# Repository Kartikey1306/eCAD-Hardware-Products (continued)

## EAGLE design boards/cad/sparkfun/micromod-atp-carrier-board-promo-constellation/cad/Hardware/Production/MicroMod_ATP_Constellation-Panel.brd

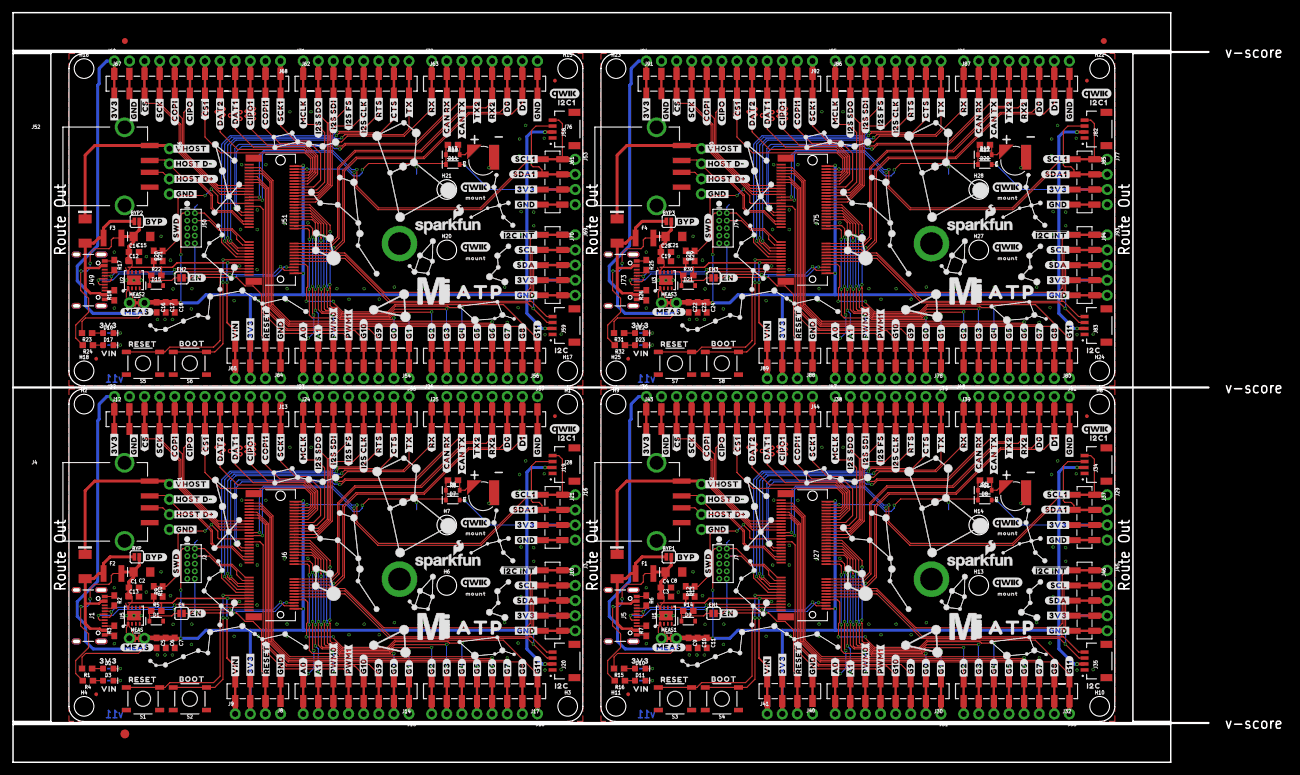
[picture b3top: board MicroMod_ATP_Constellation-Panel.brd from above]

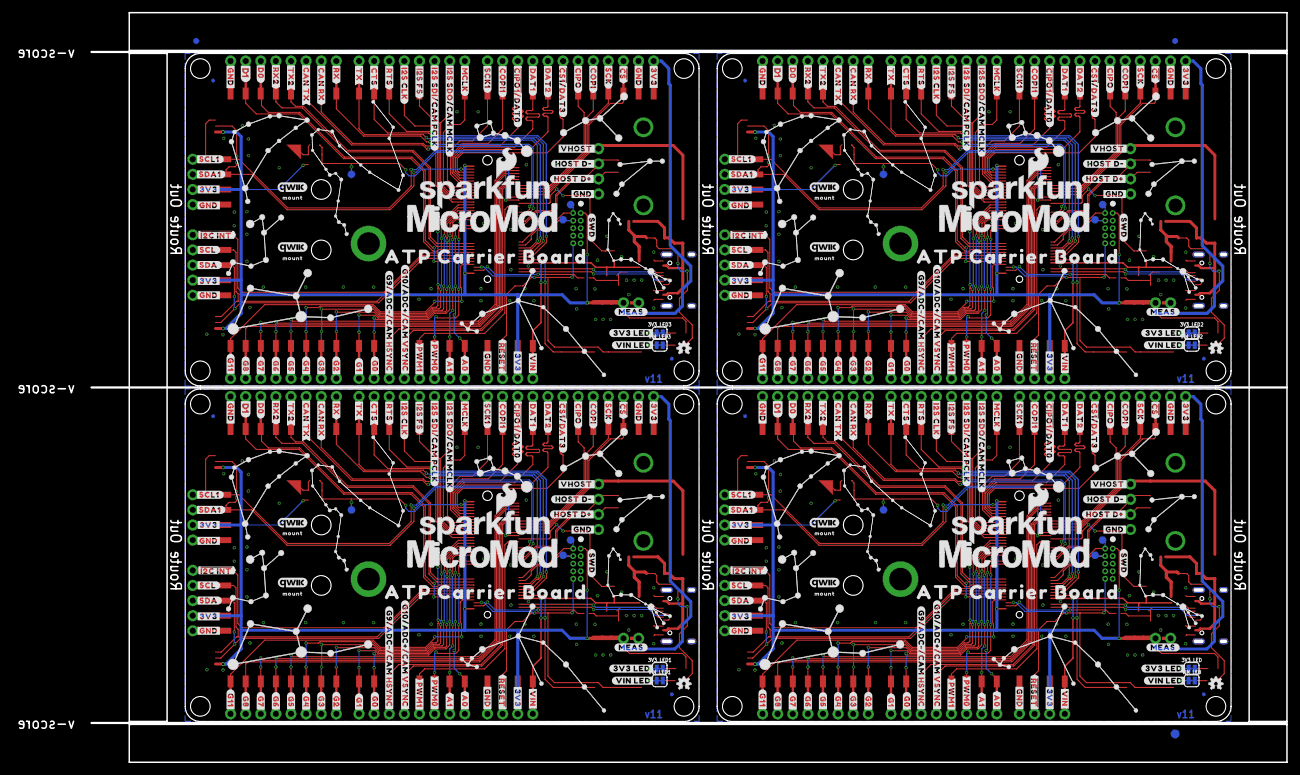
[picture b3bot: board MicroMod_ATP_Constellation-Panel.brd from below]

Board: 2 copper layers, 200.9 x 126.0 mm, 886 parts (323 on the bottom side), 284 nets.

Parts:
3V3_LED, 3V3_LED1, 3V3_LED2, 3V3_LED3: JUMPER-SMT_2_NC_TRACE_SILK; SMT-JUMPER_2_NC_TRACE_SILK
BT1, BT2, BT3, BT4: ML414H; ML414H_IV01E
BYP, BYP1, BYP2, BYP3: JUMPER-SMT_2_NO_SILK; SMT-JUMPER_2_NO_SILK
C1, C4, C6, C10, C14, C17, C20, C23: 0.1uF; 0603
C2, C8, C15, C21: 10uF; EIA3216
C3, C7, C11, C12, C13, C18, C19, C24: 0.22uF; 0603
C5, C9, C16, C22: 1.0uF; 0603
D1, D9, D15, D21: 3.3V; SOD-323
D2, D3, D10, D11, D16, D17, D22, D23: RED; LED-0603
D4, D12, D18, D24: 1A/15V/220mV; DO-214BA
D5, D6, D13, D19: 3A/10V/280mV; SOD-323
D7, D8, D14, D20: 1A/23V/620mV; SOD-323
E$1, E$2, E$3, E$4: FIDUCIAL-1X2
E$5, E$6: FIDUCIAL-1.5X3
EN, EN1, EN2, EN3: JUMPER-SMT_2_NO_SILK; SMT-JUMPER_2_NO_SILK
F1, F2, F3, F4: 6V/2A; 1210
FD1, FD2, FD3, FD4, FD5, FD6, FD7, FD8, FD9, FD10, FD11, FD12, FD13, FD14, FD15, FD16: FIDUCIALUFIDUCIAL; FIDUCIAL-MICRO
H1, H2, H3, H4, H6, H7, H8, H9, H10, H11, H13, H14, H15, H16, H17, H18, H20, H21, H22, H23, H24, H25, H27, H28: STAND-OFF
H5, H12, H19, H26: STAND-OFF-REFLOW2.5MM_TALL; STAND-OFF-REFLOW-M2.5
J1, J5, J49, J73: USB-C-16P-2LAYER-PADS
J2, J7, J50, J74: JTAG; 2X5-PTH-1.27MM
J3, J45, J69, J93: 1X05_NO_SILK
J4, J28, J52, J76: USB_A_SMT_FEMALE; USB-A-S-SILK-FEMALE
J6, J27, J51, J75: MICROMOD-2222-C; M.2-CONNECTOR-E
J8, J21, J37, J40, J61, J64, J85, J88: 1X04_SMD_STRAIGHT_COMBO; 1X04_SMD_VERTICAL_COMBO
J9, J11, J16, J22, J29, J36, J41, J42, J53, J60, J65, J66, J77, J84, J89, J90: 1X04_NO_SILK
J10, J46, J70, J94: 1X05_SMD_VERTICAL_COMBO
J12, J43, J67, J91: 1X12_SMD_COMBINED
J13, J15, J18, J23, J26, J31, J33, J44, J47, J48, J55, J57, J68, J71, J72, J79, J81, J92, J95, J96: 1X08_NO_SILK
J14, J17, J24, J25, J30, J32, J38, J39, J54, J56, J62, J63, J78, J80, J86, J87: 1X08_SMD_COMBINED
J19, J20, J34, J35, J58, J59, J82, J83: QWIIC_RIGHT_ANGLE; JST04_1MM_RA
LOGO1, LOGO11, LOGO19, LOGO27: SFE_LOGO_NAME_FLAME.1_INCH; SFE_LOGO_NAME_FLAME_.1
LOGO2, LOGO15, LOGO23, LOGO31: QWIIC_LOGO_5MM; QWIIC_5MM
LOGO3, LOGO9, LOGO17, LOGO25: OSHW-LOGOMINI; OSHW-LOGO-MINI
LOGO4, LOGO10, LOGO18, LOGO26: SFE_LOGO_NAME_FLAME.2_INCH; SFE_LOGO_NAME_FLAME_.2
LOGO5, LOGO6, LOGO7, LOGO8, LOGO12, LOGO13, LOGO14, LOGO16, LOGO20, LOGO21, LOGO22, LOGO24, LOGO28, LOGO29, LOGO30, LOGO32: QWIIC_LOGO_3MM; QWIIC_5MM
MEAS, MEAS1, MEAS2, MEAS3: COMBO-JUMPER_2_NC_TRACE
R1, R4, R8, R11, R15, R16, R19, R23, R24, R27, R31, R32: 1k; 0603
R2, R3, R6, R7, R17, R18, R25, R26: 5.1k; 0603
R5, R14, R22, R30: 100k; 0603
R9, R12, R20, R28: 10k; 0603
R10, R13, R21, R29: 20k; 0603
S1, S3, S5, S7: Reset; TACTILE_SWITCH_SMD_5.2MM
S2, S4, S6, S8: BOOT; TACTILE_SWITCH_SMD_5.2MM
TP1, TP2, TP3, TP4, TP5, TP6, TP7, TP8, TP9, TP10, TP11, TP12: TEST-POINT3X5; PAD.03X.05
U1, U2, U3, U5: AP7361C-33; UDFN-8
U$1, U$123, U$167, U$249, U$311, U$393, U$455, U$537: #A0#10
U$2, U$124, U$168, U$250, U$312, U$394, U$456, U$538: #A1#10
U$3, U$27, U$46, U$47, U$58, U$89, U$100, U$101, U$102, U$103, U$104, U$105, U$158, U$164, U$165, U$226, U$227, U$228, U$229, U$230, U$231, U$266, U$267, U$268, U$302, U$308, U$309, U$370, U$371, U$372, U$373, U$374, U$375, U$410, U$411, U$412, U$446, U$452, U$453, U$514, U$515, U$516, U$517, U$518, U$519, U$554, U$555, U$556: #GND#0
U$4, U$120, U$170, U$246, U$314, U$390, U$458, U$534: #G0#2
U$5, U$161, U$305, U$449: #RESET10
U$6, U$98, U$169, U$225, U$313, U$369, U$457, U$513: #D0#0
U$7, U$119, U$171, U$245, U$315, U$389, U$459, U$533: #G1#2
U$8, U$118, U$172, U$244, U$316, U$388, U$460, U$532: #G2#2
U$9, U$117, U$173, U$243, U$317, U$387, U$461, U$531: #G3#3
U$10, U$116, U$174, U$242, U$318, U$386, U$462, U$530: #G4#4
U$11, U$115, U$175, U$241, U$319, U$385, U$463, U$529: #G5#5
U$12, U$114, U$176, U$240, U$320, U$384, U$464, U$528: #G6#6
U$13, U$113, U$177, U$239, U$321, U$383, U$465, U$527: #G7#7
U$14, U$112, U$178, U$238, U$322, U$382, U$466, U$526: #G8#8
U$15, U$179, U$323, U$467: #G9#9
U$16, U$180, U$324, U$468: #G10#10
U$17, U$111, U$181, U$237, U$325, U$381, U$469, U$525: #G11#10
U$18, U$121, U$182, U$247, U$326, U$391, U$470, U$535: #PWM0#10
U$19, U$122, U$183, U$248, U$327, U$392, U$471, U$536: #PWM1#10
U$20, U$284, U$428, U$572: ##CS1##5178039
U$21, U$110, U$236, U$269, U$380, U$413, U$524, U$557: ##I2C_INT##10
U$22, U$55, U$289, U$433: #CAN_RX#9
U$23, U$74, U$97, U$224, U$290, U$368, U$434, U$512: #CAN_TX#10
U$24, U$130, U$291, U$435: #CIPO#3
U$25, U$148, U$292, U$436: #COPI#2
U$26, U$149, U$293, U$437: #CTS#6
U$28, U$265, U$409, U$553: #SCK#2
U$29, U$150, U$294, U$438: #I2S_FS#5
U$30, U$151, U$295, U$439: #I2S_SDI#5
U$31, U$152, U$296, U$440: #I2S_SDO#5
U$32, U$153, U$297, U$441: #MCLK#4
U$33, U$154, U$298, U$442: #RTS#5
U$34, U$155, U$299, U$443: #RX#8
U$35, U$156, U$300, U$444: #TX#7
U$36, U$285, U$429, U$573: #DAT1#5178039
U$37, U$125, U$204, U$251, U$348, U$395, U$492, U$539: ##RESET##7
U$38, U$60, U$61, U$70, U$88, U$106, U$107, U$126, U$195, U$196, U$197, U$198, U$232, U$233, U$252, U$264, U$339, U$340, U$341, U$342, U$376, U$377, U$396, U$408, U$483, U$484, U$485, U$486, U$520, U$521, U$540, U$552: #3V3#1
U$39, U$157, U$301, U$445: #BYP#8
U$40, U$128, U$159, U$254, U$303, U$398, U$447, U$542: #HOST_D##9
U$41, U$129, U$160, U$255, U$304, U$399, U$448, U$543: #HOST_D##10
U$42, U$132, U$184, U$257, U$328, U$401, U$472, U$545: #MEAS#10
U$43, U$162, U$306, U$450: BOOT10
U$44, U$108, U$185, U$234, U$329, U$378, U$473, U$522: #SDA#4
U$45, U$127, U$163, U$253, U$307, U$397, U$451, U$541: #VIN#6
U$48, U$278, U$422, U$566: #EN#0
U$49, U$109, U$166, U$235, U$310, U$379, U$454, U$523: #SCL#5
U$50, U$146, U$279, U$280, U$423, U$424, U$567, U$568: #VHOST#0
U$51, U$131, U$186, U$256, U$330, U$400, U$474, U$544: #SWD#10
U$52, U$187, U$331, U$475: #I2S_CLK#5
U$53, U$286, U$430, U$574: #DAT2#5178039
U$54, U$287, U$431, U$575: #CIPO1#5178039
U$56, U$288, U$432, U$576: ##CIPO1##DAT0#5178038
U$57, U$75, U$203, U$206, U$347, U$350, U$491, U$494: #COPI1#2
U$59, U$205, U$349, U$493: ##CS##0
U$62, U$199, U$343, U$487: ATP0
U$63, U$76, U$188, U$207, U$332, U$351, U$476, U$495: #RX2#3
U$64, U$80, U$189, U$211, U$333, U$355, U$477, U$499: #TX2#2
U$65, U$78, U$190, U$209, U$334, U$353, U$478, U$497: #SCL1#3
U$66, U$79, U$191, U$210, U$335, U$354, U$479, U$498: #SDA1#3
U$67, U$77, U$192, U$208, U$336, U$352, U$480, U$496: #SCK1#2
U$68, U$193, U$337, U$481: VIN3
U$69, U$194, U$338, U$482: 3V34
U$71, U$200, U$344, U$488: I2C4
U$72, U$201, U$345, U$489: I2C14
U$73, U$202, U$346, U$490: ATP_CARRIER_BOARD1
U$81, U$281, U$425, U$569: ##CS##5178037
U$82, U$212, U$356, U$500: #DAT2#5
U$83, U$213, U$357, U$501: #DAT1#5
U$84, U$282, U$426, U$570: ##CS1##DAT3#5178037
U$85, U$214, U$358, U$502: #COPI#4
U$86, U$215, U$359, U$503: #SCK#4
U$87, U$216, U$360, U$504: #MCLK#6
U$90, U$217, U$361, U$505: #I2S_FS#7
U$91, U$218, U$362, U$506: #I2S_CLK#7
U$92, U$219, U$363, U$507: #RTS#7
U$93, U$220, U$364, U$508: #CTS#8
U$94, U$221, U$365, U$509: #TX#9
U$95, U$222, U$366, U$510: #RX#10
U$96, U$223, U$367, U$511: #CAN_RX#10
U$99, U$145, U$270, U$277, U$414, U$421, U$558, U$565: D10
U$133, U$258, U$402, U$546: #VIN_LED#10
U$134, U$259, U$403, U$547: #3V3_LED#10
U$135, U$260, U$404, U$548: #G9#ADC##CAM_HSYNC#9
U$136, U$261, U$405, U$549: #G10#ADC##CAM_VSYNC#10
U$137, U$262, U$406, U$550: #I2S_SDI#CAM_PCLK#7
U$138, U$263, U$407, U$551: #I2S_SDO#CAM_MCLK#7
U$139, U$141, U$142, U$143, U$272, U$273, U$274, U$275, U$416, U$417, U$418, U$419, U$560, U$561, U$562, U$563: MOUNT10
U$140, U$271, U$415, U$559: MICROMOD_MI_LOGO_1
U$144, U$276, U$420, U$564: MICROMOD_LOGO_1
U$147, U$283, U$427, U$571: #CIPO#5178038
VIN_LED, VIN_LED1, VIN_LED2, VIN_LED3: JUMPER-SMT_2_NC_TRACE_SILK; SMT-JUMPER_2_NC_TRACE_SILK

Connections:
3.3V: C5.1, C6.1, C7.1, D7.A, J2.1, J3.4, J6.2, J6.74, J8.3, J9.2, J10.4, J12.1, J16.3, J19.2, J20.2, J21.3, J22.1, MEAS.2, MEAS.4, R1.2
3.3V1: C9.1, C10.1, C11.1, D8.A, J7.1, J27.2, J27.74, J29.3, J34.2, J35.2, J36.1, J37.3, J40.3, J41.2, J43.1, J45.4, J46.4, MEAS1.2, MEAS1.4, R15.2
3.3V2: C16.1, C17.1, C18.1, D14.A, J50.1, J51.2, J51.74, J53.3, J58.2, J59.2, J60.1, J61.3, J64.3, J65.2, J67.1, J69.4, J70.4, MEAS2.2, MEAS2.4, R23.2
3.3V3: C22.1, C23.1, C24.1, D20.A, J74.1, J75.2, J75.74, J77.3, J82.2, J83.2, J84.1, J85.3, J88.3, J89.2, J91.1, J93.4, J94.4, MEAS3.2, MEAS3.4, R31.2
3.3V_EN: D1.C, EN.1, R5.1, U5.5
3.3V_EN1: D9.C, EN1.1, R14.1, U1.5
3.3V_EN2: D15.C, EN2.1, R22.1, U2.5
3.3V_EN3: D21.C, EN3.1, R30.1, U3.5
!BOOT!: J6.11, S2.3, S2.4
!BOOT!1: J27.11, S4.3, S4.4
!BOOT!2: J51.11, S6.3, S6.4
!BOOT!3: J75.11, S8.3, S8.4
!CS1!/DAT1: J27.70, J43.7, J44.6
!CS1!/DAT2: J51.70, J67.7, J68.6
!CS1!/DAT3: J6.70, J12.7, J13.6
!CS1!/DAT4: J75.70, J91.7, J92.6
!CS!: J6.55, J12.3, J22.3
!CS!1: J27.55, J36.3, J43.3
!CS!2: J51.55, J60.3, J67.3
!CS!3: J75.55, J84.3, J91.3
!RESET: J2.10, J6.6, J8.2, J9.3, S1.3, S1.4
!RESET1: J7.10, J27.6, J40.2, J41.3, S3.3, S3.4
!RESET2: J50.10, J51.6, J64.2, J65.3, S5.3, S5.4
!RESET3: J74.10, J75.6, J88.2, J89.3, S7.3, S7.4
A0: J6.34, J14.8, J15.8
A1: J6.38, J14.7, J15.7
A2: J27.34, J30.8, J31.8
A3: J27.38, J30.7, J31.7
A4: J51.34, J54.8, J55.8
A5: J51.38, J54.7, J55.7
A6: J75.34, J78.8, J79.8
A7: J75.38, J78.7, J79.7
CAN_RXI: J6.41, J25.2, J26.2
CAN_RXI1: J27.41, J39.2, J48.2
CAN_RXI2: J51.41, J63.2, J72.2
CAN_RXI3: J75.41, J87.2, J96.2
CAN_TXO: J6.43, J25.3, J26.3
CAN_TXO1: J27.43, J39.3, J48.3
CAN_TXO2: J51.43, J63.3, J72.3
CAN_TXO3: J75.43, J87.3, J96.3
CIPO: J6.61, J12.6, J13.7
CIPO1: J27.61, J43.6, J44.7
CIPO1/DAT0: J6.64, J12.10, J13.3
CIPO1/DAT1: J27.64, J43.10, J44.3
CIPO1/DAT2: J51.64, J67.10, J68.3
CIPO1/DAT3: J75.64, J91.10, J92.3
CIPO2: J51.61, J67.6, J68.7
CIPO3: J75.61, J91.6, J92.7
COPI: J6.59, J12.5, J13.8
COPI1: J6.62, J12.11, J13.2
COPI2: J27.59, J43.5, J44.8
COPI3: J27.62, J43.11, J44.2
COPI4: J51.59, J67.5, J68.8
COPI5: J51.62, J67.11, J68.2
COPI6: J75.59, J91.5, J92.8
COPI7: J75.62, J91.11, J92.2
CTS1: J6.15, J23.7, J24.7
CTS2: J27.15, J38.7, J47.7
CTS3: J51.15, J62.7, J71.7
CTS4: J75.15, J86.7, J95.7
D0: J6.10, J25.6, J26.6
D1: J6.18, J25.7, J26.7
D2: J27.10, J39.6, J48.6
D3: J27.18, J39.7, J48.7
D4: J51.10, J63.6, J72.6
D5: J51.18, J63.7, J72.7
D6: J75.10, J87.6, J96.6
D7: J75.18, J87.7, J96.7
DAT1: J6.66, J12.9, J13.4
DAT2: J6.68, J12.8, J13.5
DAT3: J27.66, J43.9, J44.4
DAT4: J27.68, J43.8, J44.5
DAT5: J51.66, J67.9, J68.4
DAT6: J51.68, J67.8, J68.5
DAT7: J75.66, J91.9, J92.4
DAT8: J75.68, J91.8, J92.5
G0: J6.40, J14.2, J15.2
G1: J6.42, J14.1, J15.1
G2: J6.44, J17.8, J18.8
G3: J6.46, J17.7, J18.7
G4: J6.48, J17.6, J18.6
G5: J6.73, J17.5, J18.5
G6: J6.71, J17.4, J18.4
G7: J6.69, J17.3, J18.3
G8: J6.67, J17.2, J18.2
G9: J27.40, J30.2, J31.2
G9/ADC_N: J6.65, J14.3, J15.3
G9/ADC_N1: J27.65, J30.3, J31.3
G9/ADC_N2: J51.65, J54.3, J55.3
G9/ADC_N3: J75.65, J78.3, J79.3
G10: J27.42, J30.1, J31.1
G10/ADC_P: J6.63, J14.4, J15.4
G10/ADC_P1: J27.63, J30.4, J31.4
G10/ADC_P2: J51.63, J54.4, J55.4
G10/ADC_P3: J75.63, J78.4, J79.4
G11: J6.8, J17.1, J18.1
G12: J27.73, J32.5, J33.5
G13: J27.48, J32.6, J33.6
G14: J27.44, J32.8, J33.8
G15: J27.69, J32.3, J33.3
G16: J27.46, J32.7, J33.7
G17: J27.71, J32.4, J33.4
G18: J27.67, J32.2, J33.2
G19: J27.8, J32.1, J33.1
G20: J51.40, J54.2, J55.2
G21: J51.42, J54.1, J55.1
G22: J51.73, J56.5, J57.5
G23: J51.48, J56.6, J57.6
G24: J51.44, J56.8, J57.8
G25: J51.69, J56.3, J57.3
G26: J51.46, J56.7, J57.7
G27: J51.71, J56.4, J57.4
G28: J51.67, J56.2, J57.2
G29: J51.8, J56.1, J57.1
G30: J75.40, J78.2, J79.2
G31: J75.42, J78.1, J79.1
G32: J75.73, J80.5, J81.5
G33: J75.48, J80.6, J81.6
G34: J75.44, J80.8, J81.8
G35: J75.69, J80.3, J81.3
G36: J75.46, J80.7, J81.7
G37: J75.71, J80.4, J81.4
G38: J75.67, J80.2, J81.2
G39: J75.8, J80.1, J81.1
GND: 3V3_LED.2, BT1.-, C1.2, C2.-, C5.2, C6.2, C7.2, C13.2, D1.A, H5.1, J1.GND, J1.GND2, J2.3, J2.5, J2.9, J3.5, J4.GND, J4.SHLD1, J4.SHLD2, J6.1, J6.7, J6.33, J6.36, J6.39, J6.45, J6.75, J8.1, J9.4, J10.5, J11.4, J12.2, J16.4, J19.1, J20.1, J21.4, J22.2, J25.8, J26.8, R2.1, R3.1, R9.1, S1.1, S1.2, S2.1, S2.2, U5.4, U5.EP, VIN_LED.2
GND1: 3V3_LED1.2, BT2.-, C3.2, C4.2, C8.-, C9.2, C10.2, C11.2, D9.A, H12.1, J5.GND, J5.GND2, J7.3, J7.5, J7.9, J27.1, J27.7, J27.33, J27.36, J27.39, J27.45, J27.75, J28.GND, J28.SHLD1, J28.SHLD2, J29.4, J34.1, J35.1, J36.2, J37.4, J39.8, J40.1, J41.4, J42.4, J43.2, J45.5, J46.5, J48.8, R6.1, R7.1, R12.1, S3.1, S3.2, S4.1, S4.2, U1.4, U1.EP, VIN_LED1.2
GND2: 3V3_LED2.2, BT3.-, C12.2, C14.2, C15.-, C16.2, C17.2, C18.2, D15.A, H19.1, J49.GND, J49.GND2, J50.3, J50.5, J50.9, J51.1, J51.7, J51.33, J51.36, J51.39, J51.45, J51.75, J52.GND, J52.SHLD1, J52.SHLD2, J53.4, J58.1, J59.1, J60.2, J61.4, J63.8, J64.1, J65.4, J66.4, J67.2, J69.5, J70.5, J72.8, R17.1, R18.1, R20.1, S5.1, S5.2, S6.1, S6.2, U2.4, U2.EP, VIN_LED2.2
GND3: 3V3_LED3.2, BT4.-, C19.2, C20.2, C21.-, C22.2, C23.2, C24.2, D21.A, H26.1, J73.GND, J73.GND2, J74.3, J74.5, J74.9, J75.1, J75.7, J75.33, J75.36, J75.39, J75.45, J75.75, J76.GND, J76.SHLD1, J76.SHLD2, J77.4, J82.1, J83.1, J84.2, J85.4, J87.8, J88.1, J89.4, J90.4, J91.2, J93.5, J94.5, J96.8, R25.1, R26.1, R28.1, S7.1, S7.2, S8.1, S8.2, U3.4, U3.EP, VIN_LED3.2
I2C_!INT: J3.1, J6.16, J10.1
I2C_!INT1: J27.16, J45.1, J46.1
I2C_!INT2: J51.16, J69.1, J70.1
I2C_!INT3: J75.16, J93.1, J94.1
I2S_CLK: J6.50, J23.5, J24.5
I2S_CLK1: J27.50, J38.5, J47.5
I2S_CLK2: J51.50, J62.5, J71.5
I2S_CLK3: J75.50, J86.5, J95.5
I2S_SDI: J6.54, J23.3, J24.3
I2S_SDI1: J27.54, J38.3, J47.3
I2S_SDI2: J51.54, J62.3, J71.3
I2S_SDI3: J75.54, J86.3, J95.3
I2S_SDO: J6.56, J23.2, J24.2
I2S_SDO1: J27.56, J38.2, J47.2
I2S_SDO2: J51.56, J62.2, J71.2
I2S_SDO3: J75.56, J86.2, J95.2
I2S_WS: J6.52, J23.4, J24.4
I2S_WS1: J27.52, J38.4, J47.4
I2S_WS2: J51.52, J62.4, J71.4
I2S_WS3: J75.52, J86.4, J95.4
MCLK: J6.58, J23.1, J24.1
MCLK1: J27.58, J38.1, J47.1
MCLK2: J51.58, J62.1, J71.1
MCLK3: J75.58, J86.1, J95.1
unnamed: D2.A, R1.1
unnamed: D3.A, R4.1
unnamed: 3V3_LED.1, D2.C
unnamed: D3.C, VIN_LED.1
unnamed: EN.2, J6.4
unnamed: J5.A5, R6.2
unnamed: D4.C, J4.VBUS, J11.1
unnamed: J5.B5, R7.2
unnamed: BT2.+, D5.A, R11.1
unnamed: J1.A5, R2.2
unnamed: J1.B5, R3.2
unnamed: D10.A, R15.1
unnamed: D11.A, R16.1
unnamed: BT1.+, D6.A, R8.1
unnamed: 3V3_LED1.1, D10.C
unnamed: D11.C, VIN_LED1.1
unnamed: EN1.2, J27.4
unnamed: D12.C, J28.VBUS, J42.1
unnamed: J49.A5, R17.2
unnamed: J49.B5, R18.2
unnamed: BT3.+, D13.A, R19.1
unnamed: D16.A, R23.1
unnamed: D17.A, R24.1
unnamed: 3V3_LED2.1, D16.C
unnamed: D17.C, VIN_LED2.1
unnamed: EN2.2, J51.4
unnamed: D18.C, J52.VBUS, J66.1
unnamed: J73.A5, R25.2
unnamed: J73.B5, R26.2
unnamed: BT4.+, D19.A, R27.1
unnamed: D22.A, R31.1
unnamed: D23.A, R32.1
unnamed: 3V3_LED3.1, D22.C
unnamed: D23.C, VIN_LED3.1
unnamed: EN3.2, J75.4
unnamed: D24.C, J76.VBUS, J90.1
OUT_MEAS: MEAS.1, MEAS.3, U5.1
OUT_MEAS1: MEAS1.1, MEAS1.3, U1.1
OUT_MEAS2: MEAS2.1, MEAS2.3, U2.1
OUT_MEAS3: MEAS3.1, MEAS3.3, U3.1
PWM0: J6.32, J14.6, J15.6
PWM1: J6.47, J14.5, J15.5
PWM2: J27.32, J30.6, J31.6
PWM3: J27.47, J30.5, J31.5
PWM4: J51.32, J54.6, J55.6
PWM5: J51.47, J54.5, J55.5
PWM6: J75.32, J78.6, J79.6
PWM7: J75.47, J78.5, J79.5
RTC_3V: D6.C, D7.C, J6.72, R8.2, TP1.P$1
RTC_3V1: D5.C, D8.C, J27.72, R11.2, TP4.P$1
RTC_3V2: D13.C, D14.C, J51.72, R19.2, TP7.P$1
RTC_3V3: D19.C, D20.C, J75.72, R27.2, TP10.P$1
RTS1: J6.13, J23.6, J24.6
RTS2: J27.13, J38.6, J47.6
RTS3: J51.13, J62.6, J71.6
RTS4: J75.13, J86.6, J95.6
RX1: J6.19, J25.1, J26.1
RX2: J6.20, J25.5, J26.5
RX3: J27.19, J39.1, J48.1
RX4: J27.20, J39.5, J48.5
RX5: J51.19, J63.1, J72.1
RX6: J51.20, J63.5, J72.5
RX7: J75.19, J87.1, J96.1
RX8: J75.20, J87.5, J96.5
SCK: J6.57, J12.4, J22.4
SCK1: J6.60, J12.12, J13.1
SCK2: J27.57, J36.4, J43.4
SCK3: J27.60, J43.12, J44.1
SCK4: J51.57, J60.4, J67.4
SCK5: J51.60, J67.12, J68.1
SCK6: J75.57, J84.4, J91.4
SCK7: J75.60, J91.12, J92.1
SCL: J3.2, J6.14, J10.2, J20.4
SCL1: J6.53, J16.1, J19.4, J21.1
SCL2: J27.14, J35.4, J45.2, J46.2
SCL3: J27.53, J29.1, J34.4, J37.1
SCL4: J51.14, J59.4, J69.2, J70.2
SCL5: J51.53, J53.1, J58.4, J61.1
SCL6: J75.14, J83.4, J93.2, J94.2
SCL7: J75.53, J77.1, J82.4, J85.1
SDA: J3.3, J6.12, J10.3, J20.3
SDA1: J6.51, J16.2, J19.3, J21.2
SDA2: J27.12, J35.3, J45.3, J46.3
SDA3: J27.51, J29.2, J34.3, J37.2
SDA4: J51.12, J59.3, J69.3, J70.3
SDA5: J51.51, J53.2, J58.3, J61.2
SDA6: J75.12, J83.3, J93.3, J94.3
SDA7: J75.51, J77.2, J82.3, J85.2
SWDCK: J2.4, J6.21, TP3.P$1
SWDCK1: J7.4, J27.21, TP6.P$1
SWDCK2: J50.4, J51.21, TP9.P$1
SWDCK3: J74.4, J75.21, TP12.P$1
SWDIO: J2.2, J6.23, TP2.P$1
SWDIO1: J7.2, J27.23, TP5.P$1
SWDIO2: J50.2, J51.23, TP8.P$1
SWDIO3: J74.2, J75.23, TP11.P$1
TX1: J6.17, J23.8, J24.8
TX2: J6.22, J25.4, J26.4
TX3: J27.17, J38.8, J47.8
TX4: J27.22, J39.4, J48.4
TX5: J51.17, J62.8, J71.8
TX6: J51.22, J63.4, J72.4
TX7: J75.17, J86.8, J95.8
TX8: J75.22, J87.4, J96.4
USBHOST_N: J4.D-, J6.37, J11.2
USBHOST_N1: J27.37, J28.D-, J42.2
USBHOST_N2: J51.37, J52.D-, J66.2
USBHOST_N3: J75.37, J76.D-, J90.2
USBHOST_P: J4.D+, J6.35, J11.3
USBHOST_P1: J27.35, J28.D+, J42.3
USBHOST_P2: J51.35, J52.D+, J66.3
USBHOST_P3: J75.35, J76.D+, J90.3
USB_N: J1.A7, J1.B7, J6.5
USB_N1: J5.A7, J5.B7, J27.5
USB_N2: J49.A7, J49.B7, J51.5
USB_N3: J73.A7, J73.B7, J75.5
USB_P: J1.A6, J1.B6, J6.3
USB_P1: J5.A6, J5.B6, J27.3
USB_P2: J49.A6, J49.B6, J51.3
USB_P3: J73.A6, J73.B6, J75.3
VIN: BYP.2, C1.1, C2.+, C13.1, F2.2, J6.9, J8.4, J9.1, R4.2, R5.2, R10.2, U5.8
VIN1: BYP1.2, C3.1, C4.1, C8.+, F1.2, J27.9, J40.4, J41.1, R13.2, R14.2, R16.2, U1.8
VIN2: BYP2.2, C12.1, C14.1, C15.+, F3.2, J51.9, J64.4, J65.1, R21.2, R22.2, R24.2, U2.8
VIN3: BYP3.2, C19.1, C20.1, C21.+, F4.2, J75.9, J88.4, J89.1, R29.2, R30.2, R32.2, U3.8
VIN/1: J27.49, R12.2, R13.1
VIN/2: J51.49, R20.2, R21.1
VIN/3: J6.49, R9.2, R10.1
VIN/4: J75.49, R28.2, R29.1
V_USB: BYP.1, D4.A, F2.1, J1.VBUS1, J1.VBUS2
V_USB1: BYP1.1, D12.A, F1.1, J5.VBUS1, J5.VBUS2
V_USB2: BYP2.1, D18.A, F3.1, J49.VBUS1, J49.VBUS2
V_USB3: BYP3.1, D24.A, F4.1, J73.VBUS1, J73.VBUS2

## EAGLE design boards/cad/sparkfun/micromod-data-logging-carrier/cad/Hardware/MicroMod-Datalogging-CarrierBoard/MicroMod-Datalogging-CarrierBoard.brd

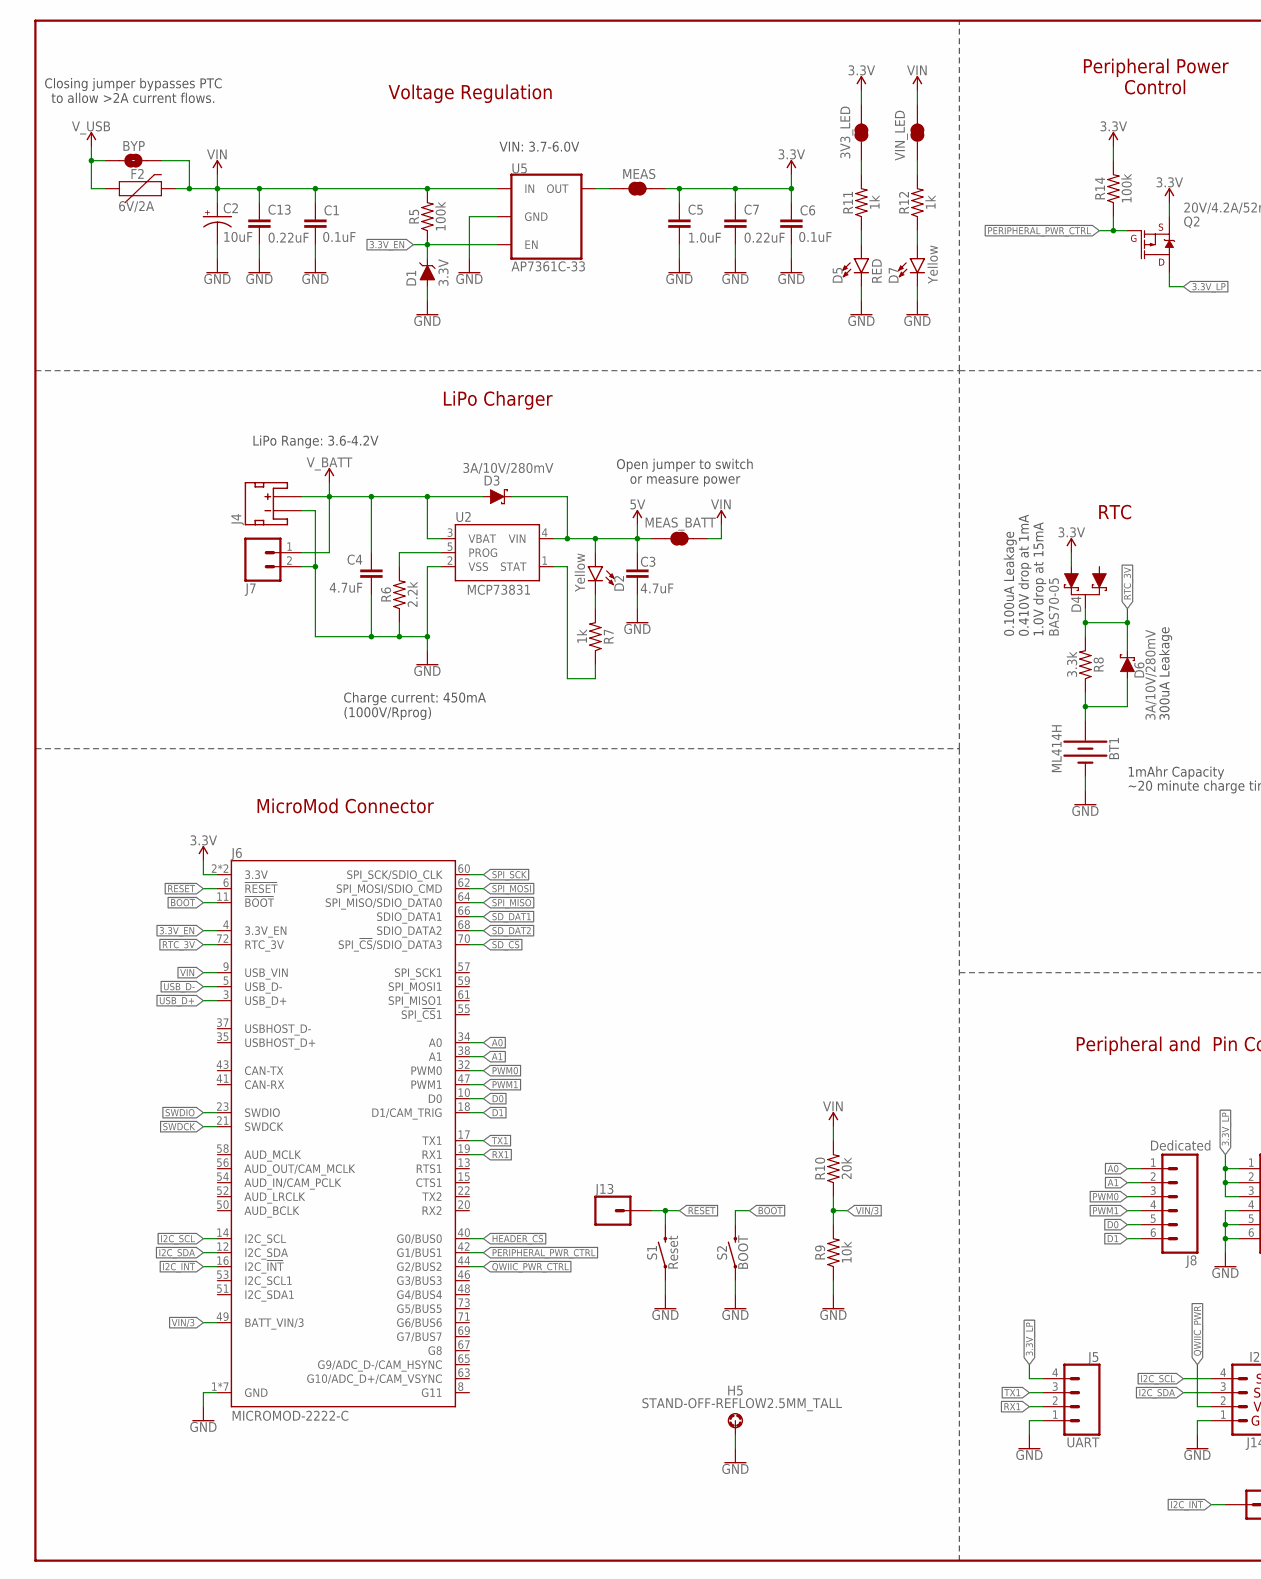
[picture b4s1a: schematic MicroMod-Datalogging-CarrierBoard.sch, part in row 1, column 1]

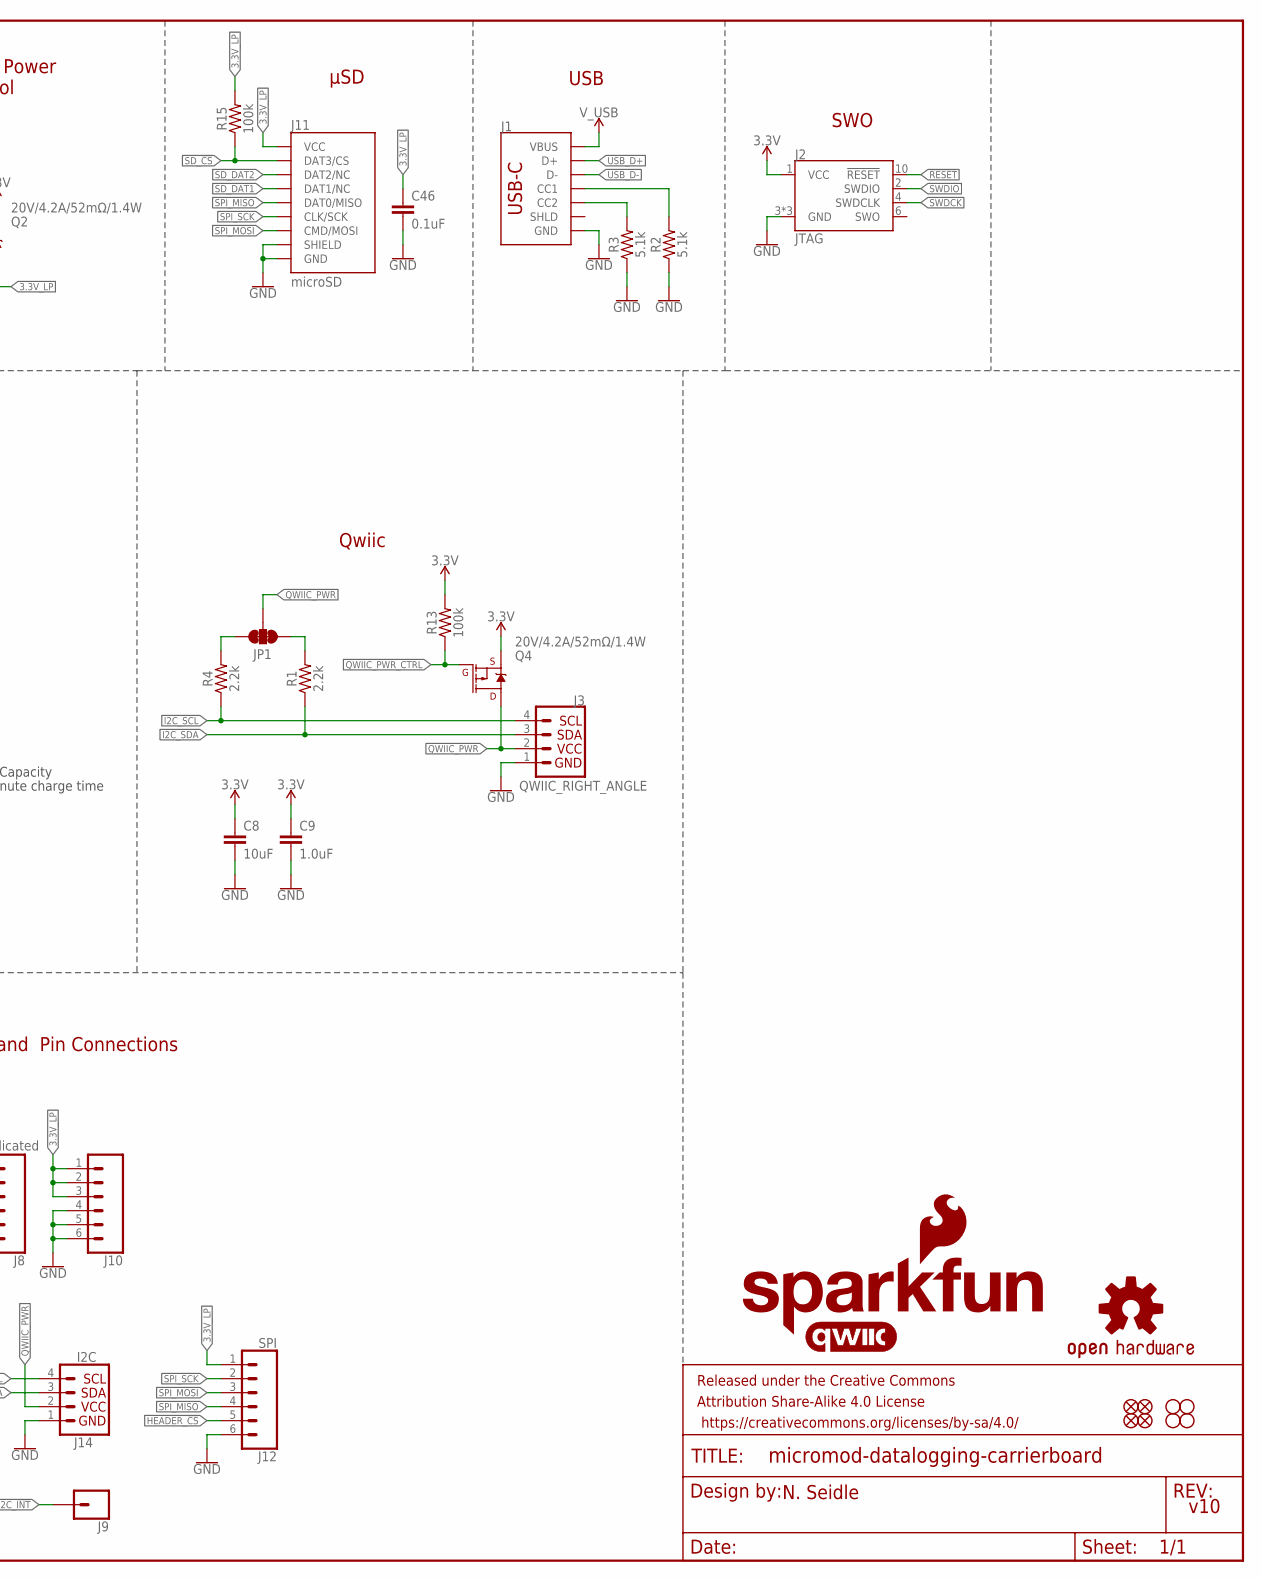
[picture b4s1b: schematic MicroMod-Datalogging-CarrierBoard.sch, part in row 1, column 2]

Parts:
3V3_LED: JUMPER-SMT_2_NC_TRACE_SILK; SMT-JUMPER_2_NC_TRACE_SILK
BT1: ML414H; ML414H_IV01E
BYP: JUMPER-SMT_2_NO_SILK; SMT-JUMPER_2_NO_SILK
C1, C6, C46: 0.1uF; 0603
C2: 10uF; EIA3216
C3, C4: 4.7uF; 0603
C5, C9: 1.0uF; 0603
C7, C13: 0.22uF; 0603
C8: 10uF; 0603
D1: 3.3V; SOD-323
D2, D7: Yellow; LED-0603
D3, D6: 3A/10V/280mV; SOD-323
D4: BAS70-05; SOT23-3
D5: RED; LED-0603
F2: 6V/2A; 1210
FD1, FD2, FD3, FD4: FIDUCIALUFIDUCIAL; FIDUCIAL-MICRO
FRAME1: FRAME-LEDGER; CREATIVE_COMMONS
H1, H2, H3, H4: STAND-OFF
H5: STAND-OFF-REFLOW2.5MM_TALL; STAND-OFF-REFLOW-M2.5
J1: USB_C_2-LAYER_PADS; USB-C-16P-2LAYER-PADS
J2: JTAG; 2X5-PTH-1.27MM
J3: QWIIC_RIGHT_ANGLE; JST04_1MM_RA
J4: JST_2MM_MALE; JST-2-SMD
J5: UART; 1X04_NO_SILK
J6: MICROMOD-2222-C; M.2-CONNECTOR-E
J7: CONN_021X02_NO_SILK; 1X02_NO_SILK
J8: Dedicated; 1X06_NO_SILK
J9, J13: CONN_01PTH_NO_SILK_YES_STOP; 1X01_NO_SILK
J10: CONN_06NO_SILK_NO_POP; 1X06_NO_SILK
J11: microSD; MICRO-SD-SOCKET
J12: SPI; 1X06_NO_SILK
J14: I2C; 1X04_NO_SILK
JP1: JUMPER-SMT_3_2-NC_TRACE_SILK; SMT-JUMPER_3_2-NC_TRACE_SILK
LOGO1: SFE_LOGO_NAME_FLAME.1_INCH; SFE_LOGO_NAME_FLAME_.1
LOGO2: QWIIC_LOGO_CONNECTOR; QWIIC_5.5MM
LOGO3: OSHW-LOGOMINI; OSHW-LOGO-MINI
MEAS: JUMPER-COMBO_2_NC_TRACE; COMBO-JUMPER_2_NC_TRACE
MEAS_BATT: JUMPER-COMBO_2_NC_TRACE; COMBO-JUMPER_2_NC_TRACE
Q2, Q4: 20V/4.2A/52mΩ/1.4W; SOT23-3
R1, R4, R6: 2.2k; 0603
R2, R3: 5.1k; 0603
R5, R13, R14, R15: 100k; 0603
R7, R11, R12: 1k; 0603
R8: 3.3k; 0603
R9: 10k; 0603
R10: 20k; 0603
S1: Reset; TACTILE_SWITCH_SMD_5.2MM
S2: BOOT; TACTILE_SWITCH_SMD_5.2MM
U2: MCP73831; SOT23-5
U5: AP7361C-33; UDFN-8
VIN_LED: JUMPER-SMT_2_NC_TRACE_SILK; SMT-JUMPER_2_NC_TRACE_SILK

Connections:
3.3V: 3V3_LED.2, C5.1, C6.1, C7.1, C8.1, C9.1, D4.2 (A1), J2.1 (VCC), J6.2 (3.3V), J6.74 (3.3V), MEAS.2, MEAS.4 (2), Q2.2 (S), Q4.2 (S), R13.2, R14.2
3.3V_EN: D1.C, J6.4 (3.3V_EN), R5.1, U5.5 (EN)
3.3V_LP: C46.1, J5.4, J10.1, J10.2, J10.3, J11.VCC, J12.1, Q2.3 (D), R15.2
5V: C3.1, D2.A, D3.C, MEAS_BATT.1, MEAS_BATT.3 (1), U2.4 (VIN)
!BOOT!: J6.11 (!BOOT!), S2.3 (2), S2.4 (2)
!RESET!: J2.10 (!RESET), J6.6 (!RESET!), J13.1, S1.3 (2), S1.4 (2)
A0: J6.34 (A0), J8.1
A1: J6.38 (A1), J8.2
CHG_LED: R7.1, U2.1 (STAT)
D0: J6.10 (D0), J8.5
D1: J6.18 (D1/CAM_TRIG), J8.6
GND: BT1.-, C1.2, C2.-, C3.2, C4.2, C5.2, C6.2, C7.2, C8.2, C9.2, C13.2, C46.2, D1.A, D5.C, D7.C, H5.1, J1.GND, J1.GND2 (GND), J2.3 (GND), J2.5 (GND), J2.9 (GND), J3.1, J4.1 (-), J5.1, J6.1 (GND), J6.7 (GND), J6.33 (GND), J6.36 (GND), J6.39 (GND), J6.45 (GND), J6.75 (GND), J7.2, J10.4, J10.5, J10.6, J11.CD1 (SHIELD), J11.GND, J11.GND1 (GND), J11.GND3 (GND), J12.6, J14.1, R2.1, R3.1, R6.1, R9.1, S1.1, S1.2 (1), S2.1, S2.2 (1), U2.2 (VSS), U5.4 (GND), U5.EP (GND)
HEADER_!CS!: J6.40 (G0/BUS0), J12.5
I2C_!INT!: J6.16 (I2C_!INT!), J9.1
I2C_SCL: J3.4, J6.14 (I2C_SCL), J14.4, R4.1
I2C_SDA: J3.3, J6.12 (I2C_SDA), J14.3, R1.1
unnamed: MEAS.1, MEAS.3 (1), U5.1 (OUT)
unnamed: JP1.3, R4.2
unnamed: JP1.1, R1.2
unnamed: D2.C, R7.2
unnamed: D5.A, R11.1
unnamed: 3V3_LED.1, R11.2
unnamed: R6.2, U2.5 (PROG)
unnamed: R12.2, VIN_LED.1
unnamed: D7.A, R12.1
unnamed: J1.A5 (CC1), R2.2
unnamed: J1.B5 (CC2), R3.2
unnamed: BT1.+, D6.A, R8.1
PERIPHERAL_PWR_CTRL: J6.42 (G1/BUS1), Q2.1 (G), R14.1
PWM0: J6.32 (PWM0), J8.3
PWM1: J6.47 (PWM1), J8.4
QWIIC_PWR: J3.2, J14.2, JP1.2, Q4.3 (D)
QWIIC_PWR_CTRL: J6.44 (G2/BUS2), Q4.1 (G), R13.1
RTC_3V: D4.3 (C), D6.C, J6.72 (RTC_3V), R8.2
RX1: J5.2, J6.19 (RX1)
SD_!CS!: J6.70 (SPI_!CS!/SDIO_DATA3), J11.CS (DAT3/CS), R15.1
SD_DAT1: J6.66 (SDIO_DATA1), J11.RSV2 (DAT1/NC)
SD_DAT2: J6.68 (SDIO_DATA2), J11.RSV1 (DAT2/NC)
SPI_MISO: J6.64 (SPI_MISO/SDIO_DATA0), J11.DO (DAT0/MISO), J12.4
SPI_MOSI: J6.62 (SPI_MOSI/SDIO_CMD), J11.DI (CMD/MOSI), J12.3
SPI_SCK: J6.60 (SPI_SCK/SDIO_CLK), J11.SCLK (CLK/SCK), J12.2
SWDCK: J2.4 (SWDCLK), J6.21 (SWDCK)
SWDIO: J2.2 (SWDIO), J6.23 (SWDIO)
TX1: J5.3, J6.17 (TX1)
USB_D+: J1.A6 (D+), J1.B6 (D+), J6.3 (USB_D+)
USB_D-: J1.A7 (D-), J1.B7 (D-), J6.5 (USB_D-)
VIN: BYP.2, C1.1, C2.+, C13.1, F2.2, J6.9 (USB_VIN), MEAS_BATT.2, MEAS_BATT.4 (2), R5.2, R10.2, U5.8 (IN), VIN_LED.2
VIN/3: J6.49 (BATT_VIN/3), R9.2, R10.1
V_BATT: C4.1, D3.A, J4.2 (+), J7.1, U2.3 (VBAT)
V_USB: BYP.1, F2.1, J1.VBUS1 (VBUS), J1.VBUS2 (VBUS)

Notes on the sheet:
μSD
300uA Leakage
~20 minute charge time
1mAhr Capacity
SWO
USB
Peripheral and Pin Connections
Qwiic
RTC
Voltage Regulation
MicroMod Connector
LiPo Charger
LiPo Range: 3.6-4.2V
Charge current: 450mA (1000V/Rprog)
Open jumper to switch or measure power
Peripheral Power Control
0.100uA Leakage 0.410V drop at 1mA 1.0V drop at 15mA
Closing jumper bypasses PTC to allow >2A current flows.
VIN: 3.7-6.0V
N. Seidle
v10

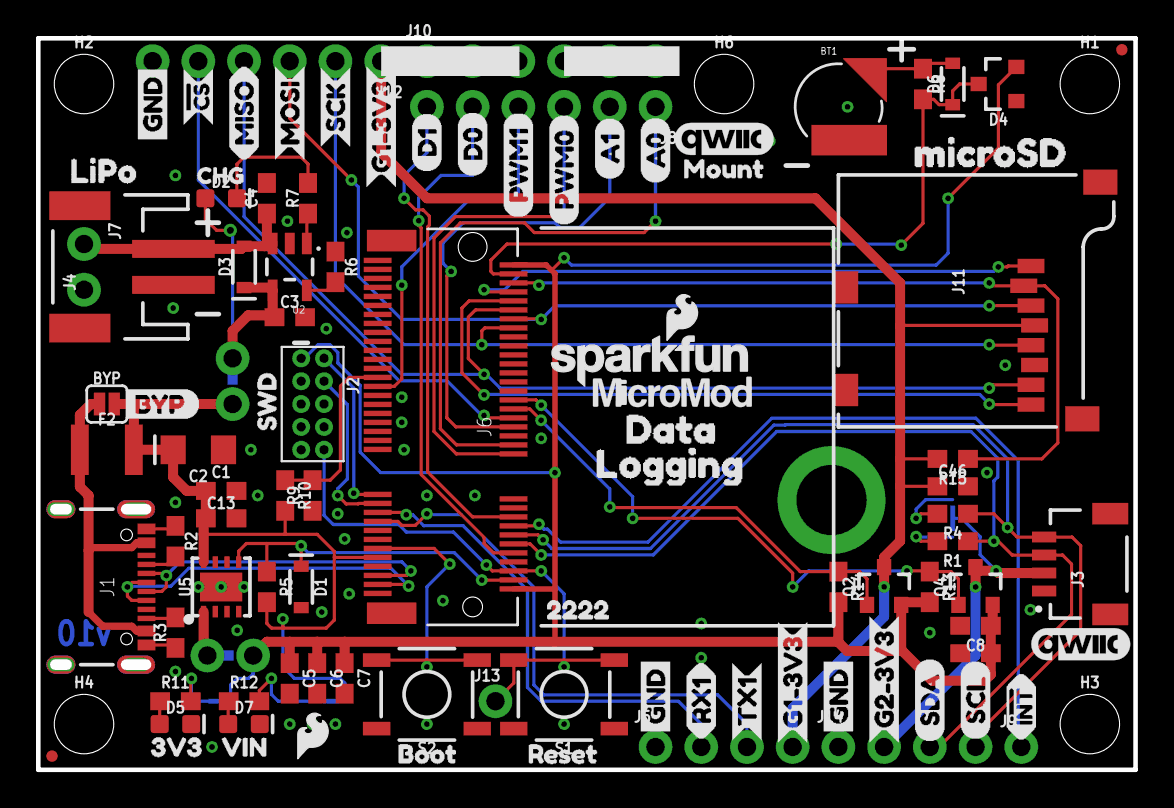
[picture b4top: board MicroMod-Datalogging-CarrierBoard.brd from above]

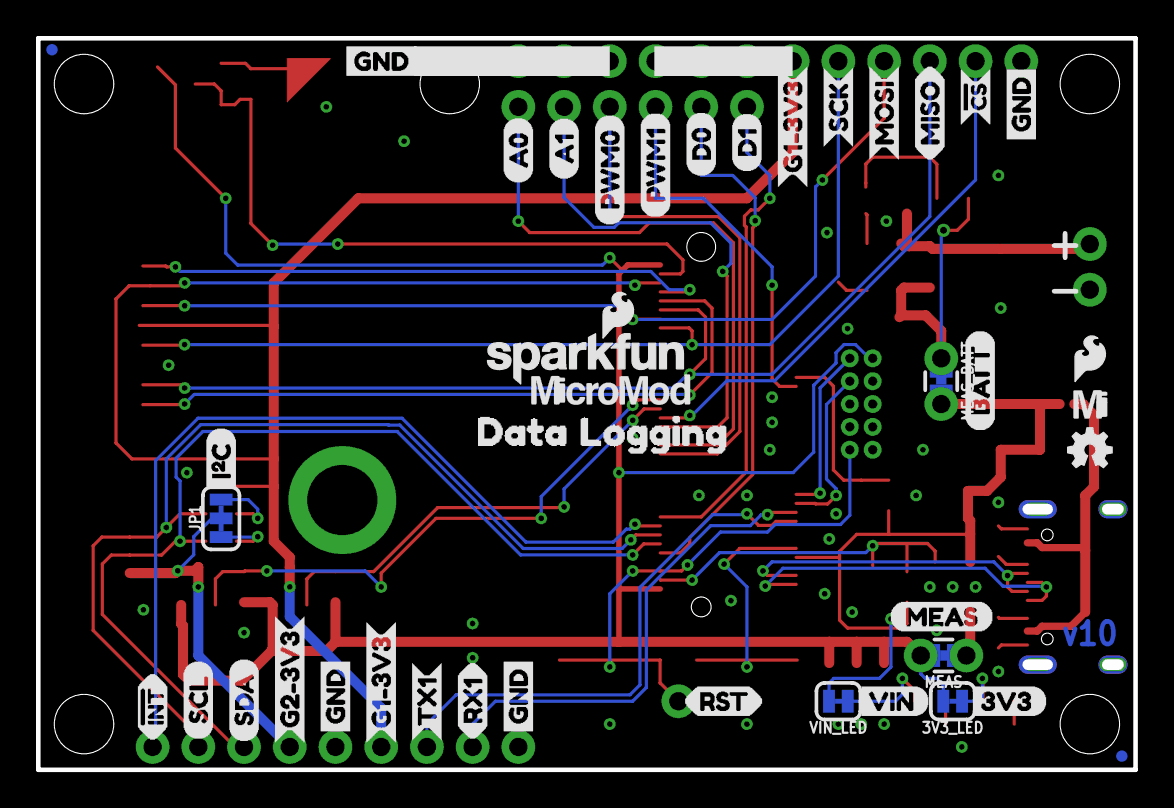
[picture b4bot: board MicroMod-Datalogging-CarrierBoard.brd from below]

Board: 2 copper layers, 61.0 x 40.6 mm, 146 parts (42 on the bottom side), 50 nets.

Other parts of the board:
H6: STAND-OFF
LOGO4: SFE_LOGO_NAME_FLAME.1_INCH; SFE_LOGO_NAME_FLAME_.1
LOGO5: QWIIC_LOGO_CONNECTOR; QWIIC_5.5MM
U$1, U$66: SFE_LOGO_FLAME_.1
U$2: RESET3
U$3, U$17, U$23, U$69: G1#3V32
U$4, U$30: DATA3
U$5: MEAS
U$6, U$32, U$36, U$42, U$45, U$53, U$54: GND_P
U$7, U$50: MOSI_O
U$8, U$51: MISO_I
U$9, U$49: SCK_O
U$10, U$52: !CS_O
U$11: MOUNT2
U$12, U$13: D13
U$14, U$16: D02
U$15, U$61: PWM10
U$18: CHG2
U$19: BOOT2
U$20: 3V3_TO
U$21, U$35: !INT_I
U$22, U$34: LOGGING4
U$24: SWD3
U$25, U$29: RX10
U$26: VIN_TO
U$27: BYP0
U$28: MICROSD4
U$31, U$41: TX13
U$33: LIPO0
U$37, U$63: MICROMOD_LOGO_.35
U$38, U$70: G2#3V31
U$39, U$47: SDA_IO
U$40, U$48: SCL_IO
U$43, U$44: A00
U$46: 3V31
U$55: 22229
U$56: I#C0
U$57, U$58: A10
U$59, U$60: PWM01
U$62: MICROMOD_MI_LOGO_.35
U$67: VIN0
U$68: RST_I
U$71: BATT1
